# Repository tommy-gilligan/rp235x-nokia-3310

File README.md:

# RP235x Nokia 3310 Adapter Board

This started as a cute "what if?":

> What if I could type out messages on my smart phone by using tactile buttons like I used to have on my phone back in high school?

Because the board would need to fit into the chassis of a Nokia 3310 and because there are existing doodads that would be sitting alongside the board anyways, scope has crept to include connecting to these other thingamajigs.

## Setting up web environment

## Setting up rp environment

## Setting up board
### Ordering Board
### Disassemble 3310
### Install Hardware Test Program
### Reassemble 3310
### Manual Test
### Install Custom Software

### TODO
#### Sooner
##### Hardware
- dress up repo
- backlight LEDs (many options but prudent to go with whatever uses least power, is simplest.  use transistor to drive LED directly from battery/power)
- Come up with better name
- double check usb footprint
- add back supercap rtc
- double check power regulation, boot button
- add jlcpcb part numbers, 3d models

C92589 switch

##### Software
- create example that plays RTTTL (and writes it to screen)
- Snake
- USB text entry
- use text_input for inputing secret for TOTP (drives the need for inputting numeric digits easily and RTC)

#### Later
- optional pico-w for wifi/bluetooth (using a module avoids need for recertification?)
    - looks like RP will release such a module (RM2) so go ahead with designing with that in mind
- detect battery type to refuse NiMH
- battery gauge
- flex pcb for keypad?
- LTE modem?
- e-ink display?
- power button used for BOOT/RUN?

https://serdisplib.sourceforge.net/ser/pcd8544.html

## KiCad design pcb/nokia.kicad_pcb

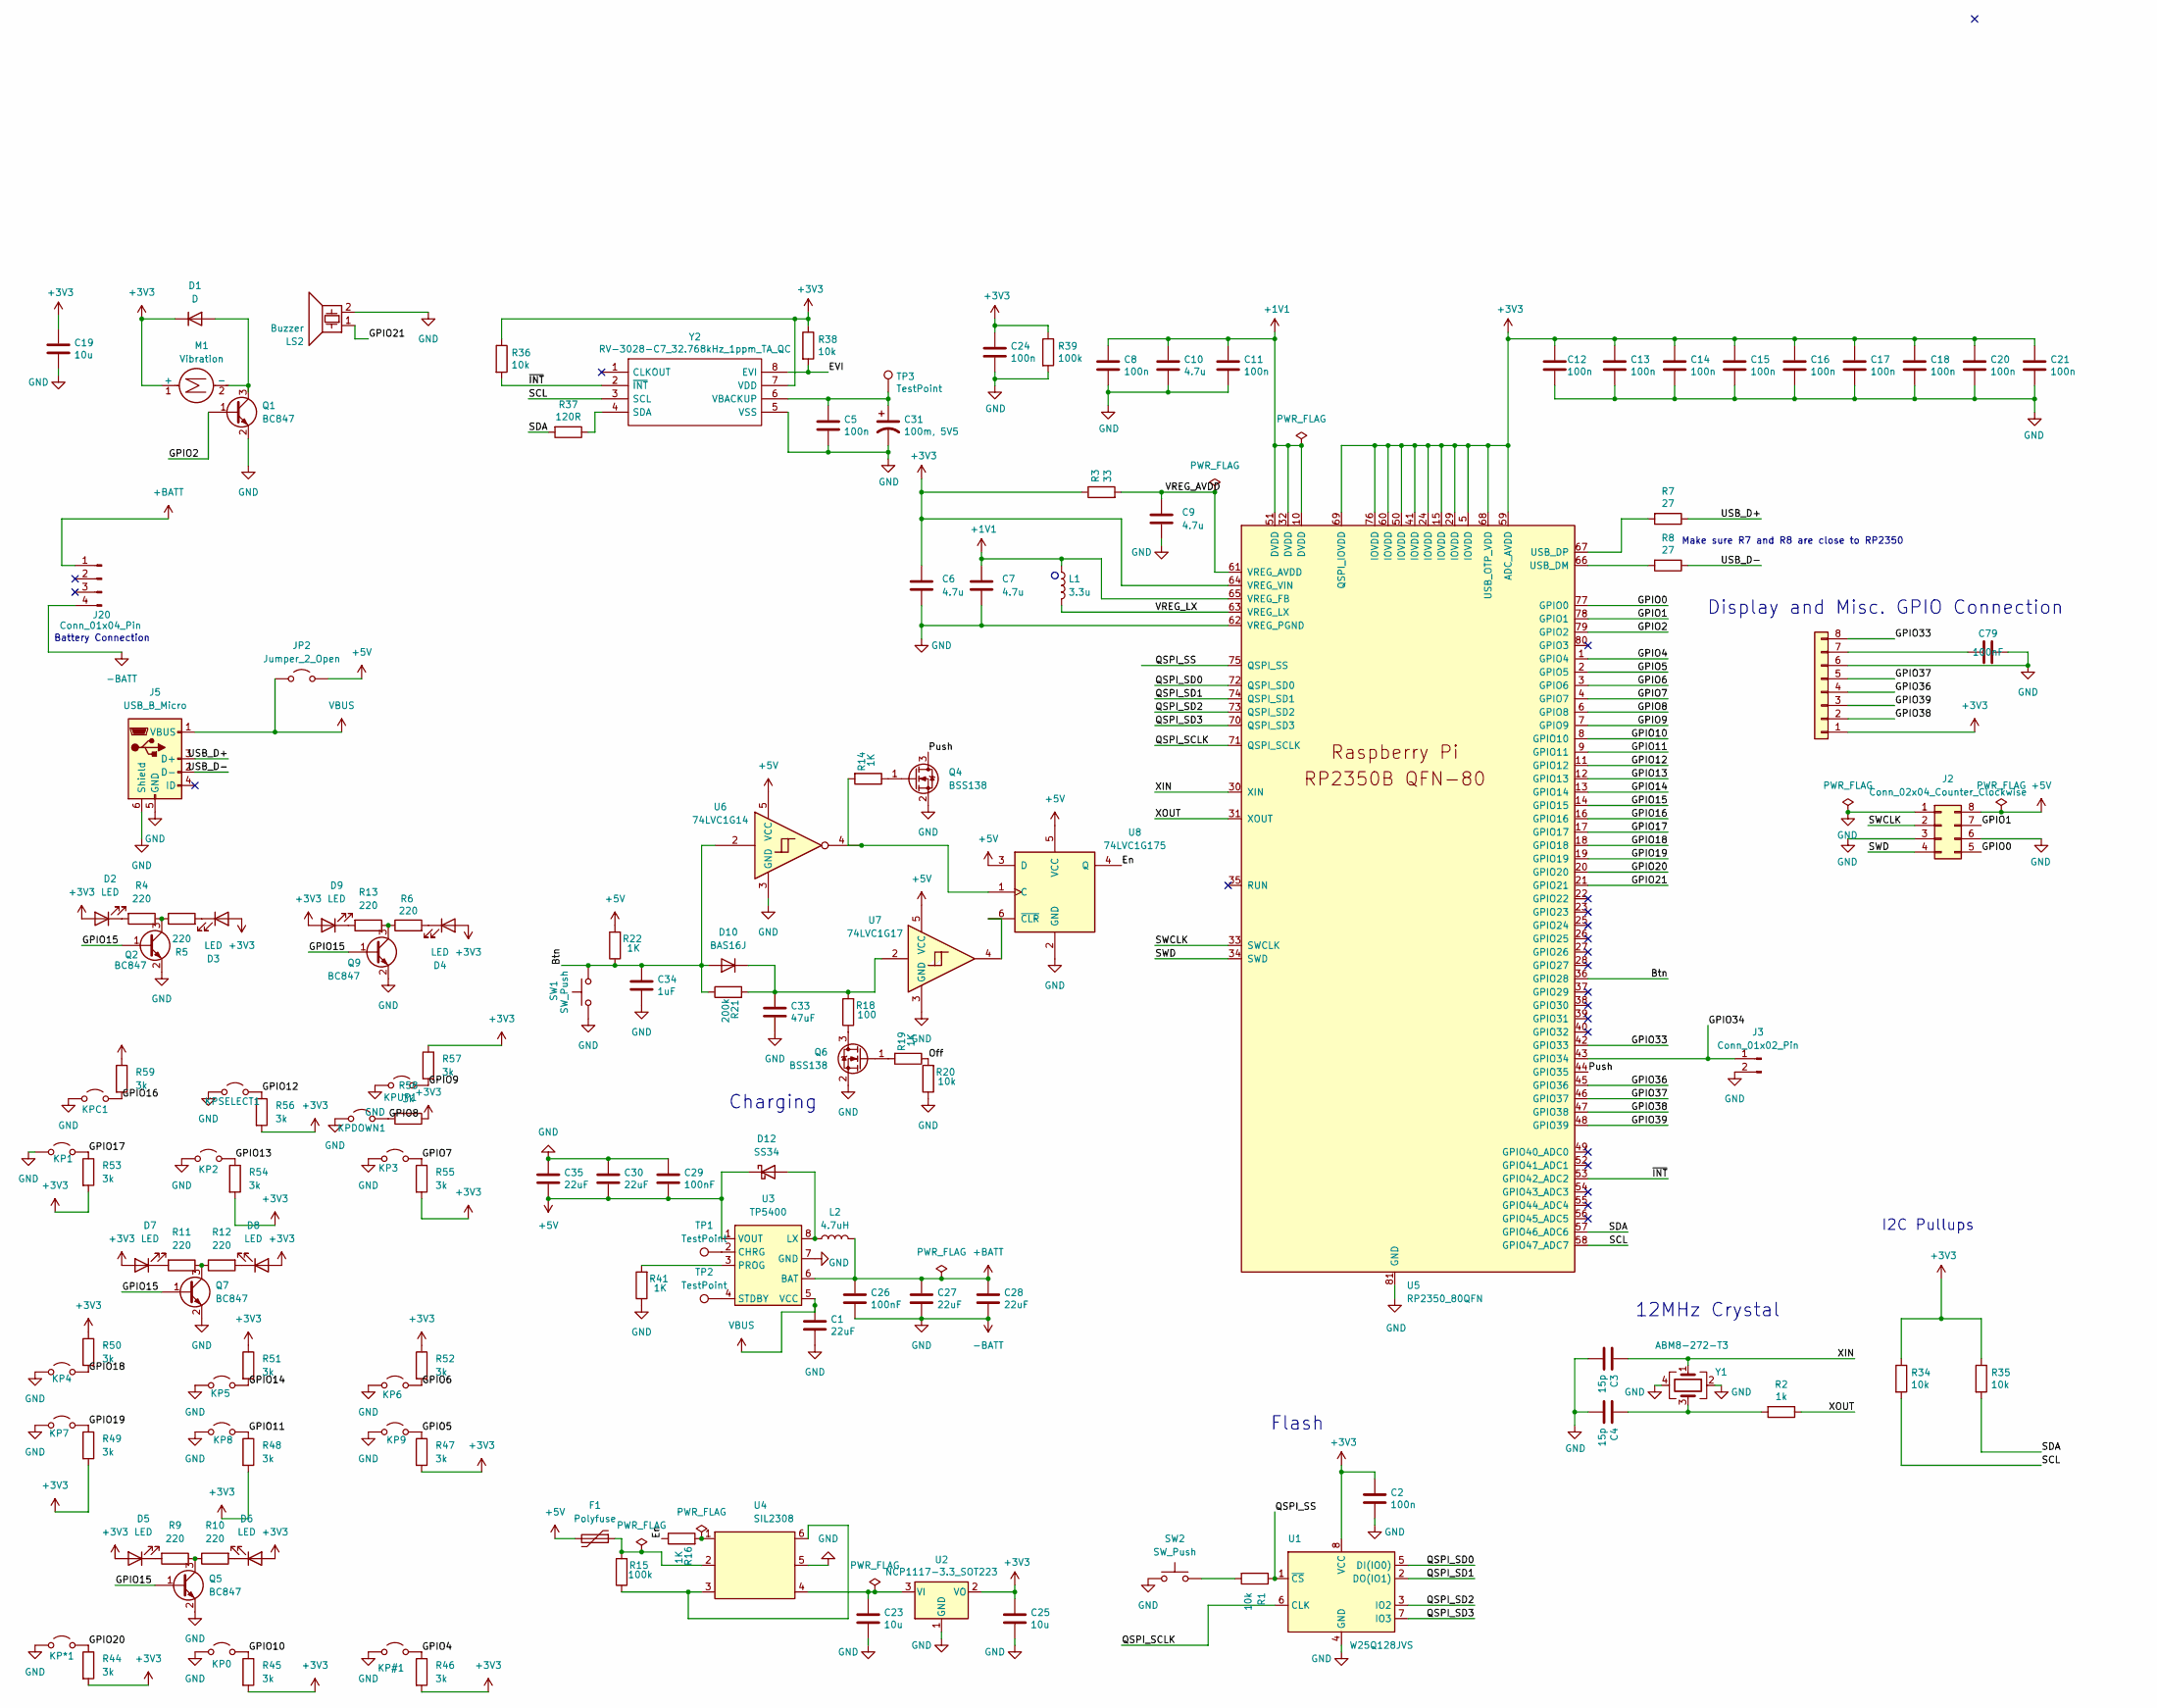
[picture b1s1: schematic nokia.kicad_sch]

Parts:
C1, C27, C28, C30, C35: 22uF; C_0805_2012Metric; JLCPCB C602037
C2, C5, C8, C11, C12, C13, C14, C15, C16, C17, C18, C20, C21, C24: 100n; C_0402_1005Metric; JLCPCB C77020
C3, C4: 15p; C_0402_1005Metric; JLCPCB C86285
C6, C7, C9, C10: 4.7u; C_0402_1005Metric; JLCPCB C368809
C19, C23, C25: 10u; C_0805_2012Metric; JLCPCB C17024
C26, C29: 100nF; C_0805_2012Metric; JLCPCB C77020
C31: 100m, 5V5; Kemet_FC_10.5X5.5
C33: 47uF; C_0805_2012Metric; JLCPCB C17024
C34: 1uF; C_0805_2012Metric; JLCPCB C17024
C79: 100nF; C_0402_1005Metric; JLCPCB C77020
D1: D; D_0402_1005Metric; JLCPCB C2837790
D2, D3, D4, D5, D6, D7, D8, D9: LED; LED_REVERSE; JLCPCB C2980185
D10: BAS16J; D_SOD-323F; JLCPCB C282360
D12: SS34; D_SMA; JLCPCB C8678
F1: Polyfuse; Fuse_Bourns_MF-SM_7.98x5.44mm; JLCPCB C2757931
J1: Conn_01x07; screen
J2: Conn_02x04_Counter_Clockwise; PinHeader_2x04_P2.54mm_Vertical_SMD
J3: Conn_01x02_Pin; PinHeader_1x02_P1.00mm_Vertical_SMD_Pin1Left
J5: USB_B_Micro; USB_Micro-B_Molex_47346-0001; JLCPCB C132560
J20: Conn_01x04_Pin; battery
JP2: Jumper_2_Open; SolderJumper-2_P1.3mm_Open_RoundedPad1.0x1.5mm
KP0, KP1, KP2, KP4, KP5, KP6, KP7, KP8, KP9: Jumper_2_Open; ButtonPads
KP3: 3; ButtonPads
KP#1: Jumper_2_Open; ButtonPads
KP*1: Jumper_2_Open; ButtonPads
KPC1: C; ButtonPads
KPDOWN1: Jumper_2_Open; ButtonPads
KPSELECT1: Jumper_2_Open; ButtonPads
KPUP1: Jumper_2_Open; ButtonPads
L1: 3.3u; L_pol_2016; JLCPCB C42411119
L2: 4.7uH; L_Neosid_MicroCoil_Ms36-L; JLCPCB C171589
LS2: Buzzer; buzzer
M1: Vibration; vibrator
Q1, Q2, Q5, Q7, Q9: BC847; SOT-23; JLCPCB C391423
Q4, Q6: BSS138; SOT-23
R1, R34, R35, R36, R38: 10k; R_0402_1005Metric; JLCPCB C60490
R2: 1k; R_0402_1005Metric; JLCPCB C25543
R3: 33; R_0402_1005Metric; JLCPCB C852729
R4, R5, R6, R9, R10, R11, R12, R13: 220; R_0402_1005Metric; JLCPCB C137872
R7, R8: 27; R_0402_1005Metric; JLCPCB C25100
R14, R16, R19, R22, R41: 1K; R_0402_1005Metric; JLCPCB C25543
R15: 100k; R_0402_1005Metric; JLCPCB C25543
R18: 100; R_0402_1005Metric; JLCPCB C25543
R20: 10k; R_0402_1005Metric; JLCPCB C25543
R21: 200k; R_0402_1005Metric; JLCPCB C25543
R37: 120R; R_0402_1005Metric; JLCPCB C114758
R39: 100k; R_0402_1005Metric; JLCPCB C60491
R44, R45, R46, R47, R48, R49, R50, R51, R52, R53, R54, R55, R56, R57, R58, R59: 3k; R_0402_1005Metric; JLCPCB C137872
SW1: SW_Push; power switch; JLCPCB C128539
SW2: SW_Push; SW_SPST_PTS810; JLCPCB C221895
TP1, TP2: TestPoint; TestPoint_THTPad_D1.5mm_Drill0.7mm
TP3: TestPoint; PinHeader_1x01_P2.54mm_Vertical
U1: W25Q128JVS; SOIC-8_5.23x5.23mm_P1.27mm; JLCPCB C97521
U2: NCP1117-3.3_SOT223; SOT-223-3_TabPin2; JLCPCB C26537
U3: TP5400; SOIC-8_3.9x4.9mm_P1.27mm; JLCPCB C2891434
U4: SIL2308; SOT-23-6
U5: RP2350_80QFN; RP2350-QFN-80-1EP_10x10_P0.4mm_EP3.4x3.4mm_ThermalVias; JLCPCB C42415655
U6: 74LVC1G14; SOT-23-5_HandSoldering
U7: 74LVC1G17; SOT-23-5_HandSoldering
U8: 74LVC1G175; TSOT-23-6_HandSoldering
Y1: ABM8-272-T3; Crystal_SMD_3225-4Pin_3.2x2.5mm; JLCPCB C20625731
Y2: RV-3028-C7_32.768kHz_1ppm_TA_QC; MicroCrystal_RV3028C7; Mouser Part Number 428-203591-MG01

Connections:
+1V1: C7.1, C8.1, C10.1, C11.1, L1.1, U5.10 (DVDD), U5.32 (DVDD), U5.51 (DVDD), U5.65 (VREG_FB)
+3V3: C2.1, C6.1, C12.1, C13.1, C14.1, C15.1, C16.1, C17.1, C18.1, C19.1, C20.1, C21.1, C24.1, C25.1, D1.1 (K), D2.2 (A), D3.2 (A), D4.2 (A), D5.2 (A), D6.2 (A), D7.2 (A), D8.2 (A), D9.2 (A), J1.1, M1.1 (+), R3.1, R34.1, R35.1, R36.1, R38.1, R39.1, R44.2, R45.2, R46.2, R47.2, R48.2, R49.2, R50.1, R51.1, R52.1, R53.2, R54.2, R55.2, R56.2, R57.1, R58.1, R59.1, U1.8 (VCC), U2.2 (VO), U5.5 (IOVDD), U5.15 (IOVDD), U5.24 (IOVDD), U5.29 (IOVDD), U5.41 (IOVDD), U5.50 (IOVDD), U5.59 (ADC_AVDD), U5.60 (IOVDD), U5.64 (VREG_VIN), U5.68 (USB_OTP_VDD), U5.69 (QSPI_IOVDD), U5.76 (IOVDD), Y2.7 (VDD)
+5V: C29.2, C30.2, C35.2, D12.1 (K), F1.2, J2.8, JP2.2 (B), R22.2, U3.1 (VOUT), U6.5 (VCC), U7.5 (VCC), U8.3 (D), U8.5 (VCC)
+BATT: C26.1, C27.1, C28.1, J20.1, L2.2, U3.6 (BAT)
-BATT: C1.2, C2.2, C3.2, C4.2, C5.2, C6.2, C7.2, C8.2, C9.2, C10.2, C11.2, C12.2, C13.2, C14.2, C15.2, C16.2, C17.2, C18.2, C19.2, C20.2, C21.2, C23.2, C24.2, C25.2, C26.2, C27.2, C28.2, C29.1, C30.1, C31.2, C33.2, C34.2, C35.1, C79.1, J1.6, J2.1, J2.3, J2.6, J3.2, J5.5 (GND), J5.6 (Shield), J20.4, KP0.1 (A), KP1.1 (A), KP2.1 (A), KP3.1 (A), KP4.1 (A), KP5.1 (A), KP6.1 (A), KP7.1 (A), KP8.1 (A), KP9.1 (A), KP#1.1 (A), KP*1.1 (A), KPC1.1 (A), KPDOWN1.1 (A), KPSELECT1.1 (A), KPUP1.1 (A), LS2.2, Q1.2 (E), Q2.2 (E), Q4.2 (S), Q5.2 (E), Q6.2 (S), Q7.2 (E), Q9.2 (E), R20.1, R39.2, R41.1, SW1.1, SW2.1, U1.4 (GND), U2.1 (GND), U3.7 (GND), U4.5, U5.62 (VREG_PGND), U5.81 (GND), U6.3 (GND), U7.3 (GND), U8.2 (GND), Y1.2, Y1.4, Y2.5 (VSS)
/Btn: C34.1, D10.2 (A), R21.1, R22.1, SW1.2, U5.36 (GPIO28), U6.2
/EVI: R38.2, Y2.8 (EVI)
/En: R16.1, U8.4 (Q)
/GPIO0: J2.5, U5.77 (GPIO0)
/GPIO1: J2.7, U5.78 (GPIO1)
/GPIO2: Q1.1 (B), U5.79 (GPIO2)
/GPIO4: KP#1.2 (B), R46.1, U5.1 (GPIO4)
/GPIO5: KP9.2 (B), R47.1, U5.2 (GPIO5)
/GPIO6: KP6.2 (B), R52.2, U5.3 (GPIO6)
/GPIO7: KP3.2 (B), R55.1, U5.4 (GPIO7)
/GPIO8: KPDOWN1.2 (B), R58.2, U5.6 (GPIO8)
/GPIO9: KPUP1.2 (B), R57.2, U5.7 (GPIO9)
/GPIO10: KP0.2 (B), R45.1, U5.8 (GPIO10)
/GPIO11: KP8.2 (B), R48.1, U5.9 (GPIO11)
/GPIO12: KPSELECT1.2 (B), R56.1, U5.11 (GPIO12)
/GPIO13: KP2.2 (B), R54.1, U5.12 (GPIO13)
/GPIO14: KP5.2 (B), R51.2, U5.13 (GPIO14)
/GPIO15: Q2.1 (B), Q5.1 (B), Q7.1 (B), Q9.1 (B), U5.14 (GPIO15)
/GPIO16: KPC1.2 (B), R59.2, U5.16 (GPIO16)
/GPIO17: KP1.2 (B), R53.1, U5.17 (GPIO17)
/GPIO18: KP4.2 (B), R50.2, U5.18 (GPIO18)
/GPIO19: KP7.2 (B), R49.1, U5.19 (GPIO19)
/GPIO20: KP*1.2 (B), R44.1, U5.20 (GPIO20)
/GPIO21: LS2.1, U5.21 (GPIO21)
/GPIO33: J1.8, U5.42 (GPIO33)
/GPIO34: J3.1, U5.43 (GPIO34)
/GPIO36: J1.4, U5.45 (GPIO36)
/GPIO37: J1.5, U5.46 (GPIO37)
/GPIO38: J1.2, U5.47 (GPIO38)
/GPIO39: J1.3, U5.48 (GPIO39)
/Off: R19.1, R20.2
/Push: Q4.3 (D), U5.44 (GPIO35)
/QSPI_SCLK: U1.6 (CLK), U5.71 (QSPI_SCLK)
/QSPI_SD0: U1.5 (DI(IO0)), U5.72 (QSPI_SD0)
/QSPI_SD1: U1.2 (DO(IO1)), U5.74 (QSPI_SD1)
/QSPI_SD2: U1.3 (IO2), U5.73 (QSPI_SD2)
/QSPI_SD3: U1.7 (IO3), U5.70 (QSPI_SD3)
/QSPI_SS: R1.1, U1.1 (~CS), U5.75 (QSPI_SS)
/SCL: R34.2, U5.58 (GPIO47_ADC7), Y2.3 (SCL)
/SDA: R35.2, R37.2, U5.57 (GPIO46_ADC6)
/SWCLK: J2.2, U5.33 (SWCLK)
/SWD: J2.4, U5.34 (SWD)
/USB_D+: J5.3 (D+), R7.1
/USB_D-: J5.2 (D-), R8.1
/VREG_AVDD: C9.1, R3.2, U5.61 (VREG_AVDD)
/VREG_LX: L1.2, U5.63 (VREG_LX)
/XIN: C3.1, U5.30 (XIN), Y1.1
/XOUT: R2.1, U5.31 (XOUT)
/~INT: R36.2, U5.53 (GPIO42_ADC2), Y2.2 (~INT)
unnamed: C4.1, R2.2, Y1.3
unnamed: D1.2 (A), M1.2 (-), Q1.3 (C)
unnamed: D2.1 (K), R4.2
unnamed: D3.1 (K), R5.2
unnamed: D4.1 (K), R6.2
unnamed: D5.1 (K), R9.2
unnamed: D6.1 (K), R10.2
unnamed: D7.1 (K), R11.2
unnamed: D8.1 (K), R12.2
unnamed: D9.1 (K), R13.2
unnamed: C33.1, D10.1 (K), R18.2, R21.2, U7.2
unnamed: D12.2 (A), L2.1, U3.8 (LX)
unnamed: F1.1, R15.2, U4.2
unnamed: C79.2, J1.7
unnamed: Q2.3 (C), R4.1, R5.1
unnamed: Q4.1 (G), R14.1
unnamed: Q5.3 (C), R9.1, R10.1
unnamed: Q6.3 (D), R18.1
unnamed: Q6.1 (G), R19.2
unnamed: Q7.3 (C), R11.1, R12.1
unnamed: Q9.3 (C), R6.1, R13.1
unnamed: R1.2, SW2.2
unnamed: R15.1, U4.3, U4.6
unnamed: R16.2, U4.1
unnamed: C23.1, U2.3 (VI), U4.4
unnamed: TP1.1, U3.2 (CHRG)
unnamed: R41.2, U3.3 (PROG)
unnamed: TP2.1, U3.4 (STDBY)
unnamed: R8.2, U5.66 (USB_DM)
unnamed: R7.2, U5.67 (USB_DP)
unnamed: R14.2, U6.4, U8.1 (C)
unnamed: U7.4, U8.6 (~CLR)
unnamed: R37.1, Y2.4 (SDA)
unnamed: C5.1, C31.1, TP3.1, Y2.6 (VBACKUP)
VBUS: C1.1, J5.1 (VBUS), JP2.1 (A), U3.5 (VCC)

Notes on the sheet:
Make sure R7 and R8 are close to RP2350
I2C Pullups
Flash
Display and Misc. GPIO Connection
Charging
Battery Connection
12MHz Crystal

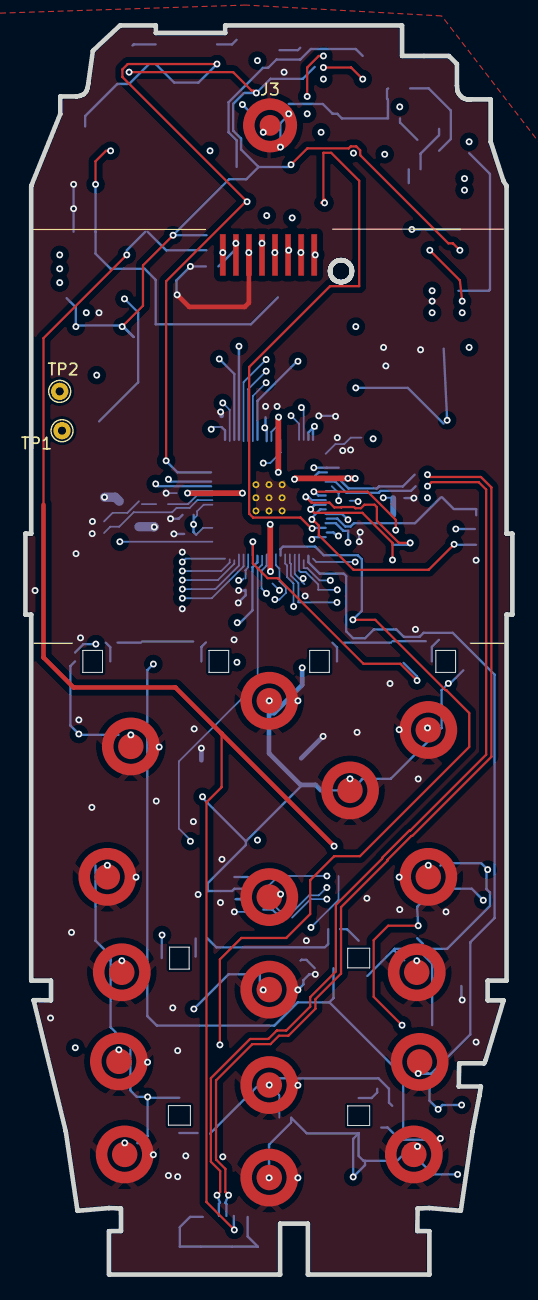
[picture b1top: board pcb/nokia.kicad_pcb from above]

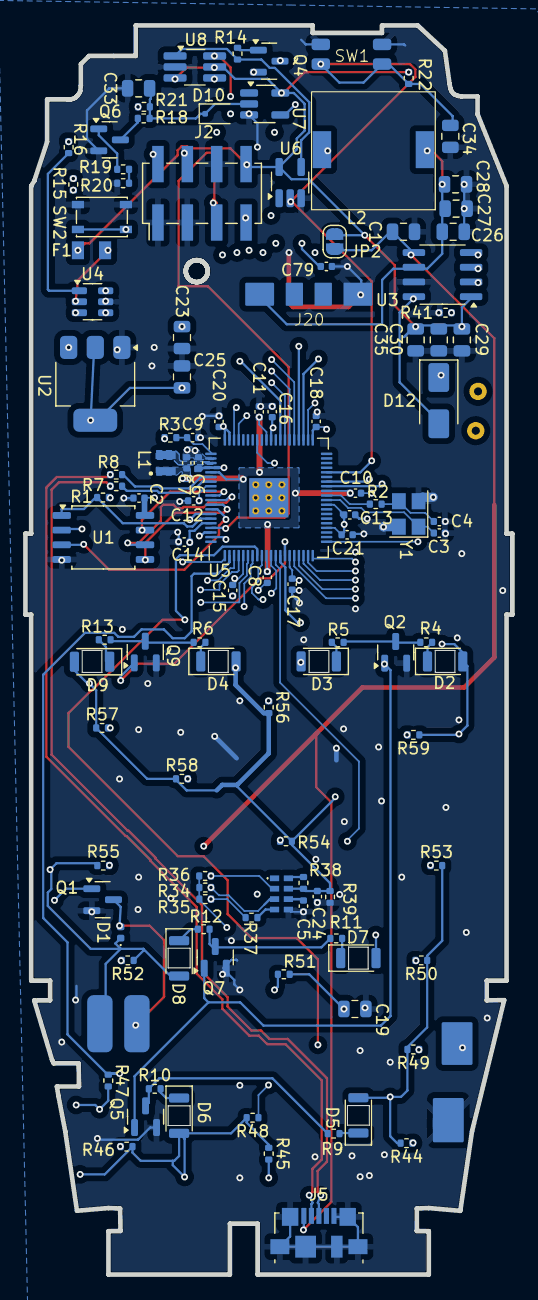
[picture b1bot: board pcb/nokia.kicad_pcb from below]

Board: 4 copper layers, 42.1 x 108.0 mm, 136 parts (116 on the bottom side), 89 nets.

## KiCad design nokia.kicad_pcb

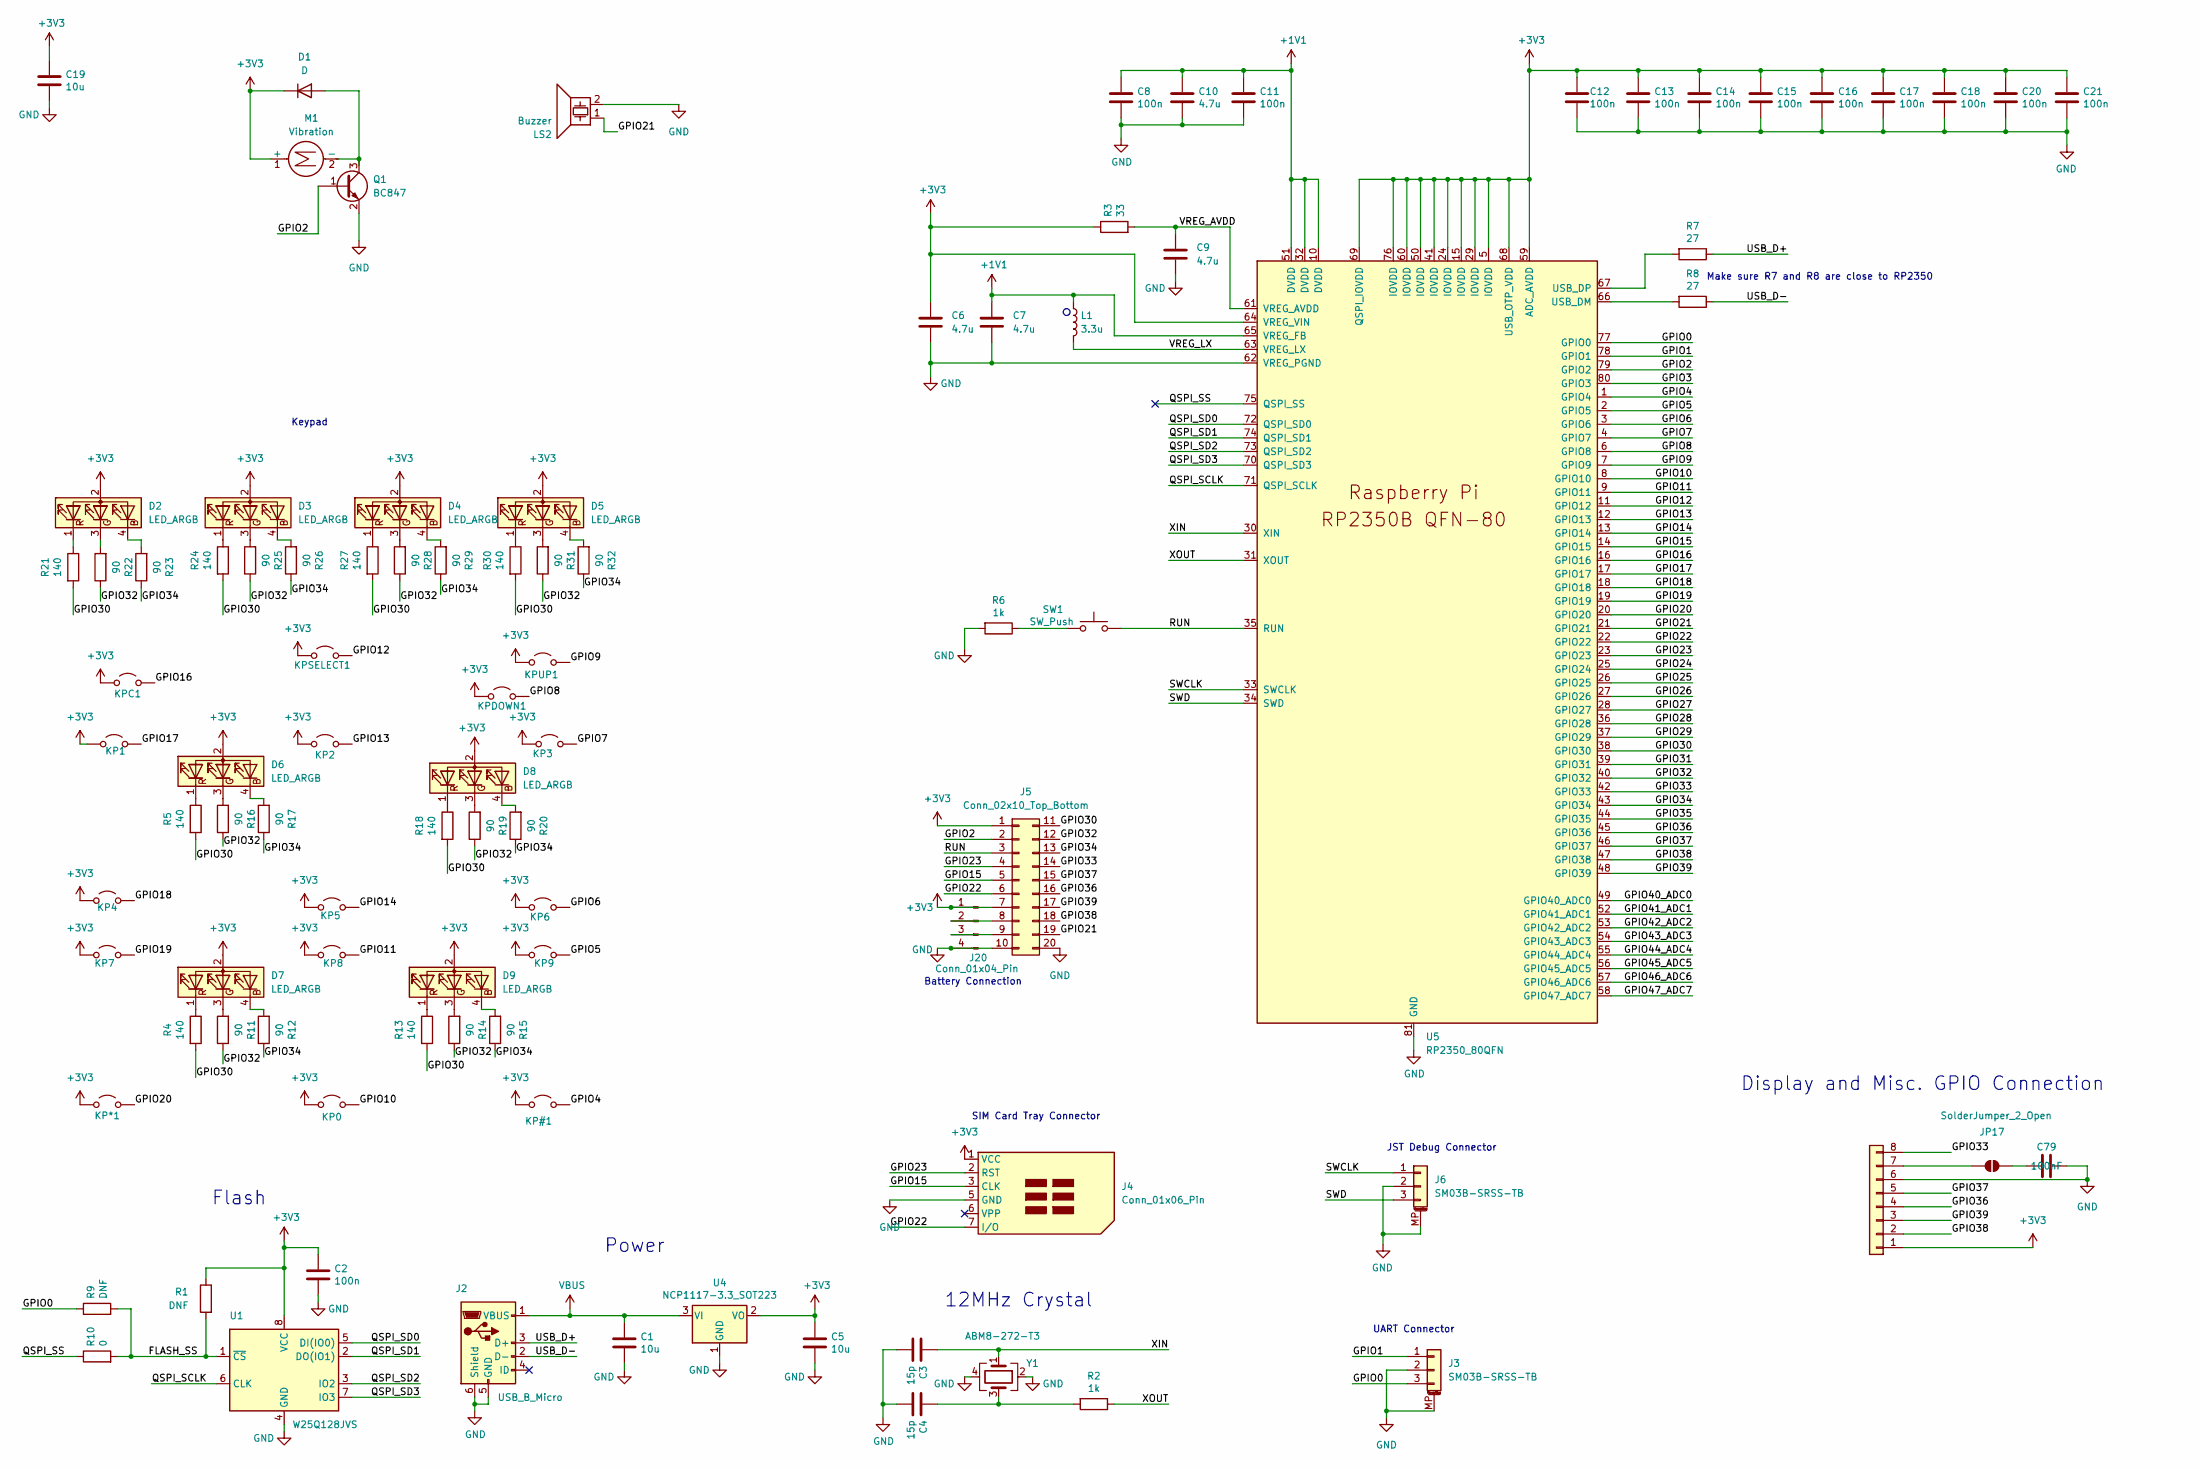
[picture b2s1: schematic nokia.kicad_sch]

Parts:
C1, C5, C19: 10u; C_0805_2012Metric
C2, C8, C11, C12, C13, C14, C15, C16, C17, C18, C20, C21: 100n; C_0402_1005Metric
C3, C4: 15p; C_0402_1005Metric
C6, C7, C9, C10: 4.7u; C_0402_1005Metric
C79: 100nF; C_0402_1005Metric
D1: D; D_0402_1005Metric
D2, D3, D4, D5, D6, D7, D8, D9: LED_ARGB; RGBLED-reverse
J1: Conn_01x07; screen
J2: USB_B_Micro; USB_Micro-B_Amphenol_10103594-0001LF_Horizontal
J3, J6: SM03B-SRSS-TB; JST_SH_SM03B-SRSS-TB_1x03-1MP_P1.00mm_Horizontal
J4: Conn_01x06_Pin; sim connector connector
J5: Conn_02x10_Top_Bottom; PinHeader_2x10_P2.54mm_Vertical_SMD
J20: Conn_01x04_Pin; battery
JP17: SolderJumper_2_Open; SolderJumper-2_P1.3mm_Open_RoundedPad1.0x1.5mm
KP0, KP1, KP2, KP4, KP5, KP6, KP7, KP8, KP9: Jumper_2_Open; ButtonPads
KP3: 3; ButtonPads
KP#1: Jumper_2_Open; ButtonPads
KP*1: Jumper_2_Open; ButtonPads
KPC1: C; ButtonPads
KPDOWN1: Jumper_2_Open; ButtonPads
KPSELECT1: Jumper_2_Open; ButtonPads
KPUP1: Jumper_2_Open; ButtonPads
L1: 3.3u; L_pol_2016
LS2: Buzzer; buzzer
M1: Vibration; vibrator
Q1: BC847; SOT-23
R1, R9: DNF; R_0402_1005Metric
R2, R6: 1k; R_0402_1005Metric
R3: 33; R_0402_1005Metric
R4, R5, R13, R18, R21, R24, R27, R30: 140; R_0402_1005Metric
R7, R8: 27; R_0402_1005Metric
R10: 0; R_0402_1005Metric
R11, R12, R14, R15, R16, R17, R19, R20, R22, R23, R25, R26, R28, R29, R31, R32: 90; R_0402_1005Metric
SW1: SW_Push; power switch
U1: W25Q128JVS; SOIC-8_5.23x5.23mm_P1.27mm
U4: NCP1117-3.3_SOT223; SOT-223-3_TabPin2
U5: RP2350_80QFN; RP2350-QFN-80-1EP_10x10_P0.4mm_EP3.4x3.4mm_ThermalVias
Y1: ABM8-272-T3; Crystal_SMD_3225-4Pin_3.2x2.5mm

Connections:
+1V1: C7.1, C8.1, C10.1, C11.1, L1.1, U5.10 (DVDD), U5.32 (DVDD), U5.51 (DVDD), U5.65 (VREG_FB)
+3V3: C2.1, C5.1, C6.1, C12.1, C13.1, C14.1, C15.1, C16.1, C17.1, C18.1, C19.1, C20.1, C21.1, D1.1 (K), D2.2, D3.2 (A), D4.2 (A), D5.2 (A), D6.2 (A), D7.2 (A), D8.2 (A), D9.2 (A), J1.1, J4.1 (VCC), J5.1, J5.7, J20.1, KP0.1 (A), KP1.1 (A), KP2.1 (A), KP3.1 (A), KP4.1 (A), KP5.1 (A), KP6.1 (A), KP7.1 (A), KP8.1 (A), KP9.1 (A), KP#1.1 (A), KP*1.1 (A), KPC1.1 (A), KPDOWN1.1 (A), KPSELECT1.1 (A), KPUP1.1 (A), M1.1 (+), R1.1, R3.1, U1.8 (VCC), U4.2 (VO), U5.5 (IOVDD), U5.15 (IOVDD), U5.24 (IOVDD), U5.29 (IOVDD), U5.41 (IOVDD), U5.50 (IOVDD), U5.59 (ADC_AVDD), U5.60 (IOVDD), U5.64 (VREG_VIN), U5.68 (USB_OTP_VDD), U5.69 (QSPI_IOVDD), U5.76 (IOVDD)
/FLASH_SS: R1.2, R9.2, R10.2, U1.1 (~CS)
/GPIO0: J3.3, R9.1, U5.77 (GPIO0)
/GPIO1: J3.1, U5.78 (GPIO1)
/GPIO2: J5.2, Q1.1 (B), U5.79 (GPIO2)
/GPIO3: U5.80 (GPIO3)
/GPIO4: KP#1.2 (B), U5.1 (GPIO4)
/GPIO5: KP9.2 (B), U5.2 (GPIO5)
/GPIO6: KP6.2 (B), U5.3 (GPIO6)
/GPIO7: KP3.2 (B), U5.4 (GPIO7)
/GPIO8: KPDOWN1.2 (B), U5.6 (GPIO8)
/GPIO9: KPUP1.2 (B), U5.7 (GPIO9)
/GPIO10: KP0.2 (B), U5.8 (GPIO10)
/GPIO11: KP8.2 (B), U5.9 (GPIO11)
/GPIO12: KPSELECT1.2 (B), U5.11 (GPIO12)
/GPIO13: KP2.2 (B), U5.12 (GPIO13)
/GPIO14: KP5.2 (B), U5.13 (GPIO14)
/GPIO15: J4.3 (CLK), J5.5, U5.14 (GPIO15)
/GPIO16: KPC1.2 (B), U5.16 (GPIO16)
/GPIO17: KP1.2 (B), U5.17 (GPIO17)
/GPIO18: KP4.2 (B), U5.18 (GPIO18)
/GPIO19: KP7.2 (B), U5.19 (GPIO19)
/GPIO20: KP*1.2 (B), U5.20 (GPIO20)
/GPIO21: J5.19, LS2.1, U5.21 (GPIO21)
/GPIO22: J4.7 (I/O), J5.6, U5.22 (GPIO22)
/GPIO23: J4.2 (RST), J5.4, U5.23 (GPIO23)
/GPIO24: U5.25 (GPIO24)
/GPIO25: U5.26 (GPIO25)
/GPIO26: U5.27 (GPIO26)
/GPIO27: U5.28 (GPIO27)
/GPIO28: U5.36 (GPIO28)
/GPIO29: U5.37 (GPIO29)
/GPIO30: J5.11, R4.2, R5.2, R13.2, R18.2, R21.2, R24.2, R27.2, R30.2, U5.38 (GPIO30)
/GPIO31: U5.39 (GPIO31)
/GPIO32: J5.12, R11.1, R14.1, R16.1, R19.1, R22.1, R25.1, R28.1, R31.1, U5.40 (GPIO32)
/GPIO33: J1.8, J5.14, U5.42 (GPIO33)
/GPIO34: J5.13, R12.1, R15.1, R17.1, R20.1, R23.1, R26.1, R29.1, R32.1, U5.43 (GPIO34)
/GPIO35: U5.44 (GPIO35)
/GPIO36: J1.4, J5.16, U5.45 (GPIO36)
/GPIO37: J1.5, J5.15, U5.46 (GPIO37)
/GPIO38: J1.2, J5.18, U5.47 (GPIO38)
/GPIO39: J1.3, J5.17, U5.48 (GPIO39)
/GPIO40_ADC0: U5.49 (GPIO40_ADC0)
/GPIO41_ADC1: U5.52 (GPIO41_ADC1)
/GPIO42_ADC2: U5.53 (GPIO42_ADC2)
/GPIO43_ADC3: U5.54 (GPIO43_ADC3)
/GPIO44_ADC4: U5.55 (GPIO44_ADC4)
/GPIO45_ADC5: U5.56 (GPIO45_ADC5)
/GPIO46_ADC6: U5.57 (GPIO46_ADC6)
/GPIO47_ADC7: U5.58 (GPIO47_ADC7)
/QSPI_SCLK: U1.6 (CLK), U5.71 (QSPI_SCLK)
/QSPI_SD0: U1.5 (DI(IO0)), U5.72 (QSPI_SD0)
/QSPI_SD1: U1.2 (DO(IO1)), U5.74 (QSPI_SD1)
/QSPI_SD2: U1.3 (IO2), U5.73 (QSPI_SD2)
/QSPI_SD3: U1.7 (IO3), U5.70 (QSPI_SD3)
/QSPI_SS: R10.1, U5.75 (QSPI_SS)
/RUN: J5.3, SW1.2, U5.35 (RUN)
/SWCLK: J6.1, U5.33 (SWCLK)
/SWD: J6.3, U5.34 (SWD)
/USB_D+: J2.3 (D+), R7.1
/USB_D-: J2.2 (D-), R8.1
/VREG_AVDD: C9.1, R3.2, U5.61 (VREG_AVDD)
/VREG_LX: L1.2, U5.63 (VREG_LX)
/XIN: C3.1, U5.30 (XIN), Y1.1
/XOUT: R2.1, U5.31 (XOUT)
GND: C1.2, C2.2, C3.2, C4.2, C5.2, C6.2, C7.2, C8.2, C9.2, C10.2, C11.2, C12.2, C13.2, C14.2, C15.2, C16.2, C17.2, C18.2, C19.2, C20.2, C21.2, C79.1, J1.6, J2.5 (GND), J2.6 (Shield), J3.2, J3.MP (MountPin), J4.5 (GND), J5.10, J5.20, J6.2, J6.MP (MountPin), J20.4, LS2.2, Q1.2 (E), R6.2, U1.4 (GND), U4.1 (GND), U5.62 (VREG_PGND), U5.81 (GND), Y1.2, Y1.4
unnamed: C4.1, R2.2, Y1.3
unnamed: D1.2 (A), M1.2 (-), Q1.3 (C)
unnamed: D2.4 (BK), R23.2
unnamed: D2.3 (GK), R22.2
unnamed: D2.1, R21.1
unnamed: D3.4 (BK), R26.2
unnamed: D3.3 (GK), R25.2
unnamed: D3.1 (RK), R24.1
unnamed: D4.4 (BK), R29.2
unnamed: D4.3 (GK), R28.2
unnamed: D4.1 (RK), R27.1
unnamed: D5.4 (BK), R32.2
unnamed: D5.3 (GK), R31.2
unnamed: D5.1 (RK), R30.1
unnamed: D6.4 (BK), R17.2
unnamed: D6.3 (GK), R16.2
unnamed: D6.1 (RK), R5.1
unnamed: D7.4 (BK), R12.2
unnamed: D7.3 (GK), R11.2
unnamed: D7.1 (RK), R4.1
unnamed: D8.4 (BK), R20.2
unnamed: D8.3 (GK), R19.2
unnamed: D8.1 (RK), R18.1
unnamed: D9.4 (BK), R15.2
unnamed: D9.3 (GK), R14.2
unnamed: D9.1 (RK), R13.1
unnamed: J1.7, JP17.1 (A)
unnamed: J5.8, J20.2
unnamed: J5.9, J20.3
unnamed: C79.2, JP17.2 (B)
unnamed: R6.1, SW1.1
unnamed: R8.2, U5.66 (USB_DM)
unnamed: R7.2, U5.67 (USB_DP)
VBUS: C1.1, J2.1 (VBUS), U4.3 (VI)

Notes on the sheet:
Make sure R7 and R8 are close to RP2350
UART Connector
Flash
JST Debug Connector
SIM Card Tray Connector
Display and Misc. GPIO Connection
Keypad
Battery Connection
12MHz Crystal
Power

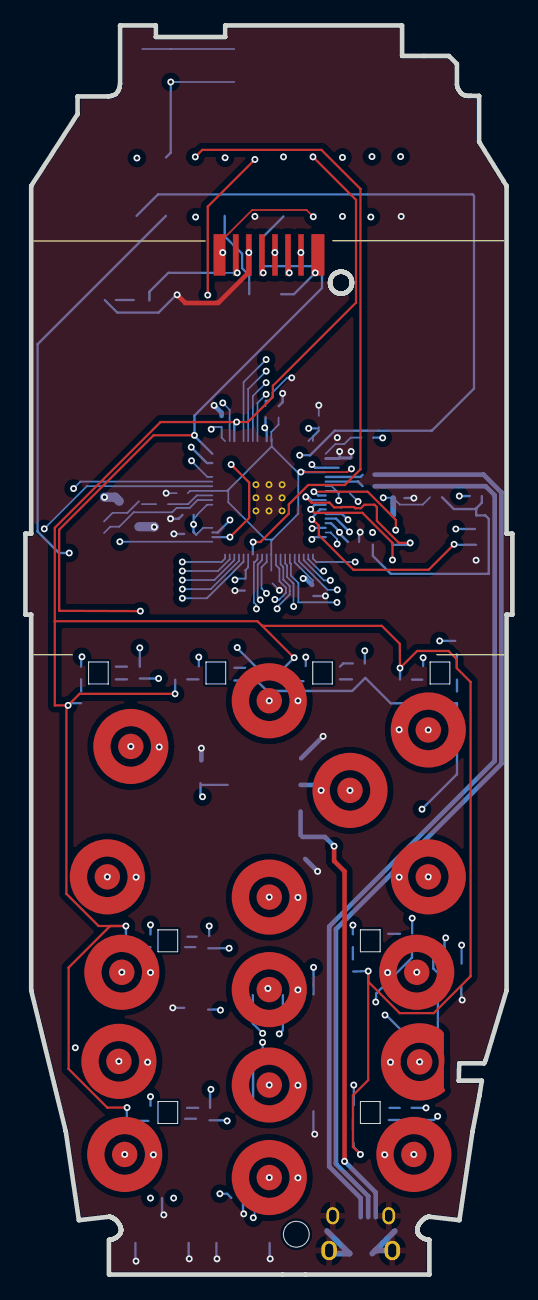
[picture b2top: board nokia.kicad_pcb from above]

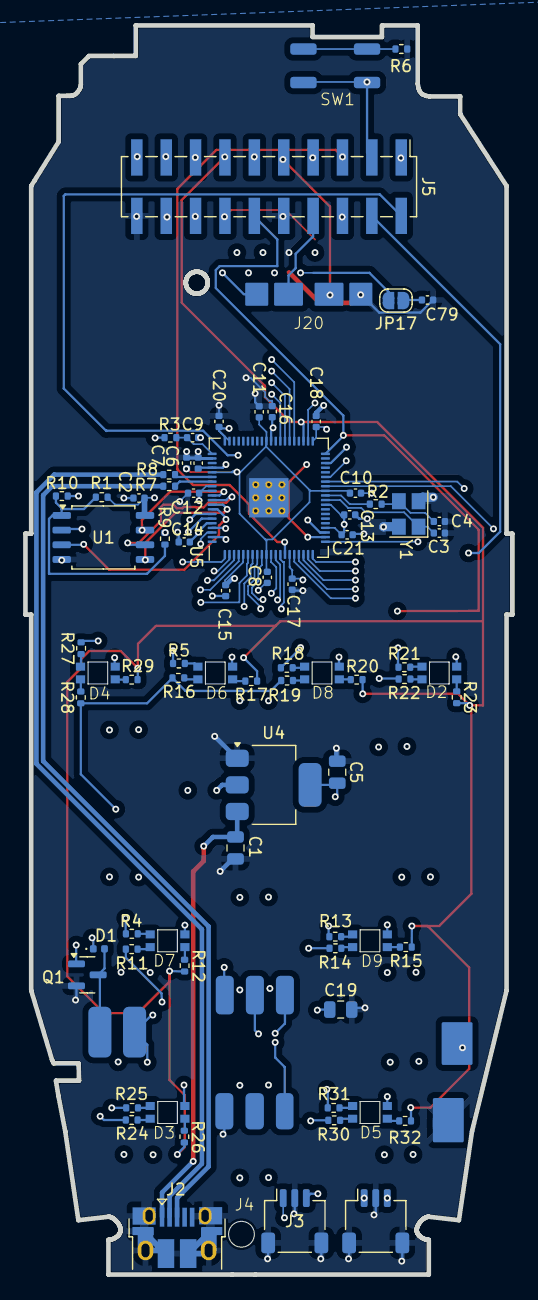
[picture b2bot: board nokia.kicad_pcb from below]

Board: 4 copper layers, 42.1 x 108.0 mm, 95 parts (78 on the bottom side), 83 nets.

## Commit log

2024-08-25 first (public) iteration of board
2024-08-25 add license
2024-08-25 add 3d preview of board
2024-08-26 add a keypad library
2024-08-27 add embassy main
2024-08-27 usb keyboard
2024-09-06 2nd iteration of board
2024-09-06 add display
2024-09-06 embedded-graphics
2024-09-06 sound
2024-09-06 more sound
2024-09-06 breadboard pinout
2024-09-06 Revert "more sound"
    This reverts commit 2d6fc62123d8b8c26e3f52d195ee75382c64a918.
2024-09-06 fixup! breadboard pinout
2024-09-09 add breakout connector
2024-09-11 part
2024-09-12 update readme, renders
2024-09-12 multitap
2024-09-12 use fascimile
2024-09-12 async matrix
2024-09-12 matrix
2024-09-12 crop renders
2024-09-16 improve display driver
2024-09-16 cleanup and start adding virtual
2024-09-16 wrapping text
2024-09-17 power button can be gpio or run
2024-09-17 split out main
2024-09-17 add web target
2024-09-17 rename main => rp
2024-09-17 separate out app
2024-09-17 start menu
2024-09-17 more menu
2024-09-17 add buzzer trait
2024-09-18 dom keypad
2024-09-18 tidy up
2024-09-20 snake
2024-09-20 use snake in rp
2024-09-29 fix and refactor snake, format
2024-09-29 add otp app
2024-10-06 jlcpcb
2024-10-09 make corrections
2024-10-09 bring back multitap
2024-10-10 switch to 235xa
2024-11-15 remove prototyping connector
2024-11-15 remove display cap jumper
2024-11-15 switch
2024-11-15 fix clearance for screws, more space for connectors, move LEDs
2024-11-16 update renders, use zone for 1v1 net
2024-11-27 add rtc and gauge, regulator
2024-11-29 first version of pcb with 2350 finished
2025-02-19 pcb v0.2
2025-02-21 update roadmap
2025-02-25 lint
2025-02-25 make apps interruptible, give access to display
2025-02-26 keypad
2025-02-26 copy web/dist to /docs
2025-02-26 publish page via action
2025-02-26 add kicad to ci
2025-02-26 update edition, rust-toolchain, rust-docs
2025-02-26 cargo update, fill out picotool info
2025-02-27 add clock
2025-02-27 add backlight to sw
2025-02-27 lint/format
2025-02-27 move time setting outside of app trait
2025-02-27 app menu
2025-02-27 remove embassy-keypad
2025-02-28 pcb v0.3
